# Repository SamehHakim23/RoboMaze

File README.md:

# RoboMaze — Autonomous Maze-Solving Robot

**ECNG 4504 — Embedded Systems for Wireless Communications**  
AUC Spring 2026 | Team 2

---

## Team Members

| Name | Student ID | Email |
|---|---|---|
| Sameh Ahmed | 900211681 | samehahmedhakim@aucegypt.edu |
| Hamza El Meadawy | 900211560 | hamzaelmeadwy@aucegypt.edu |
| Mariam Moataz | 900213249 | mariammoataz@aucegypt.edu |
| Menna AbdelHamed | 900212035 | mennnaa12@aucegypt.edu |

---

## Project Overview

RoboMaze is a fully autonomous maze-solving robot built on the ESP32 microcontroller. It uses a 5-sensor infrared array to follow black lines and navigate a maze autonomously across four sequential runs with no human intervention after the initial start command:

1. **LHR (Run 1)** — Explores the maze using the Left-Hand Rule, recording all junctions and decisions
2. **Back (Run 2)** — Returns to start along a simplified reverse path
3. **Run 2 (Run 3)** — Re-navigates the maze on the shortest discovered path using Manhattan distance heuristic
4. **Back 2 (Run 4)** — Returns to start along the optimized path

A live web application visualizes the maze map in real time and allows full wireless control via WiFi or Bluetooth BLE.

---

## Repository Structure

RoboMaze/
├── Firmware/           # ESP32 C++ source code (PlatformIO + Arduino)
├── Hardware(KiCad)/    # KiCad hardware schematic
├── Webapp/             # React + TypeScript web application
└── Docs/               # Architecture diagrams, contribution docs, team details

---

## Hardware

| Component | Model | Role |
|---|---|---|
| Microcontroller | ESP32 DevKit V1 | Main compute, WiFi 802.11, BLE 4.2 |
| IR Sensors | TCRT5000 × 5 | Line detection array |
| Motor Driver | L298N | Dual H-bridge PWM motor control |
| DC Motors | 25GA370 130RPM × 2 | Differential drive |
| Wheel Encoders | Hall-effect × 2 | Corridor distance measurement |

---

## Firmware

**Platform:** PlatformIO + Arduino Framework  
**Language:** C++  

Key features:
- Left-Hand Rule maze exploration with junction recording
- Triplet path simplification algorithm
- Run 2 Manhattan distance navigation with axis-priority selection
- WebSocket server on port 81 with full JSON telemetry protocol
- BLE GATT server with TX notify and RX write characteristics
- Encoder-based corridor distance measurement with auto-calibration

```ini
lib_deps =
    links2004/WebSockets@^2.4.0
    bblanchon/ArduinoJson@^6.21.0
board_build.partitions = huge_app.csv
```

---

## Web Application

**Stack:** React + TypeScript + Vite (frontend), Express (backend)  
**URL:** robomaze.net

Features:
- Live maze map with proportional corridor rendering
- Real-time sensor display and robot state indicator
- Full robot control panel (start, back, run2, back2, pause, e-stop)
- WiFi mode: direct browser → `ws://172.20.10.9:81`
- BLE mode: Web Bluetooth API (Chrome desktop)

---

## Wireless Communication

| Channel | Details |
|---|---|
| WiFi | Static IP 172.20.10.9 · WebSocket port 81 |
| BLE | Device: RoboMaze · Service UUID: 12345678-1234-1234-1234-123456789abc |
| Telnet | Port 23 · Raw log streaming |

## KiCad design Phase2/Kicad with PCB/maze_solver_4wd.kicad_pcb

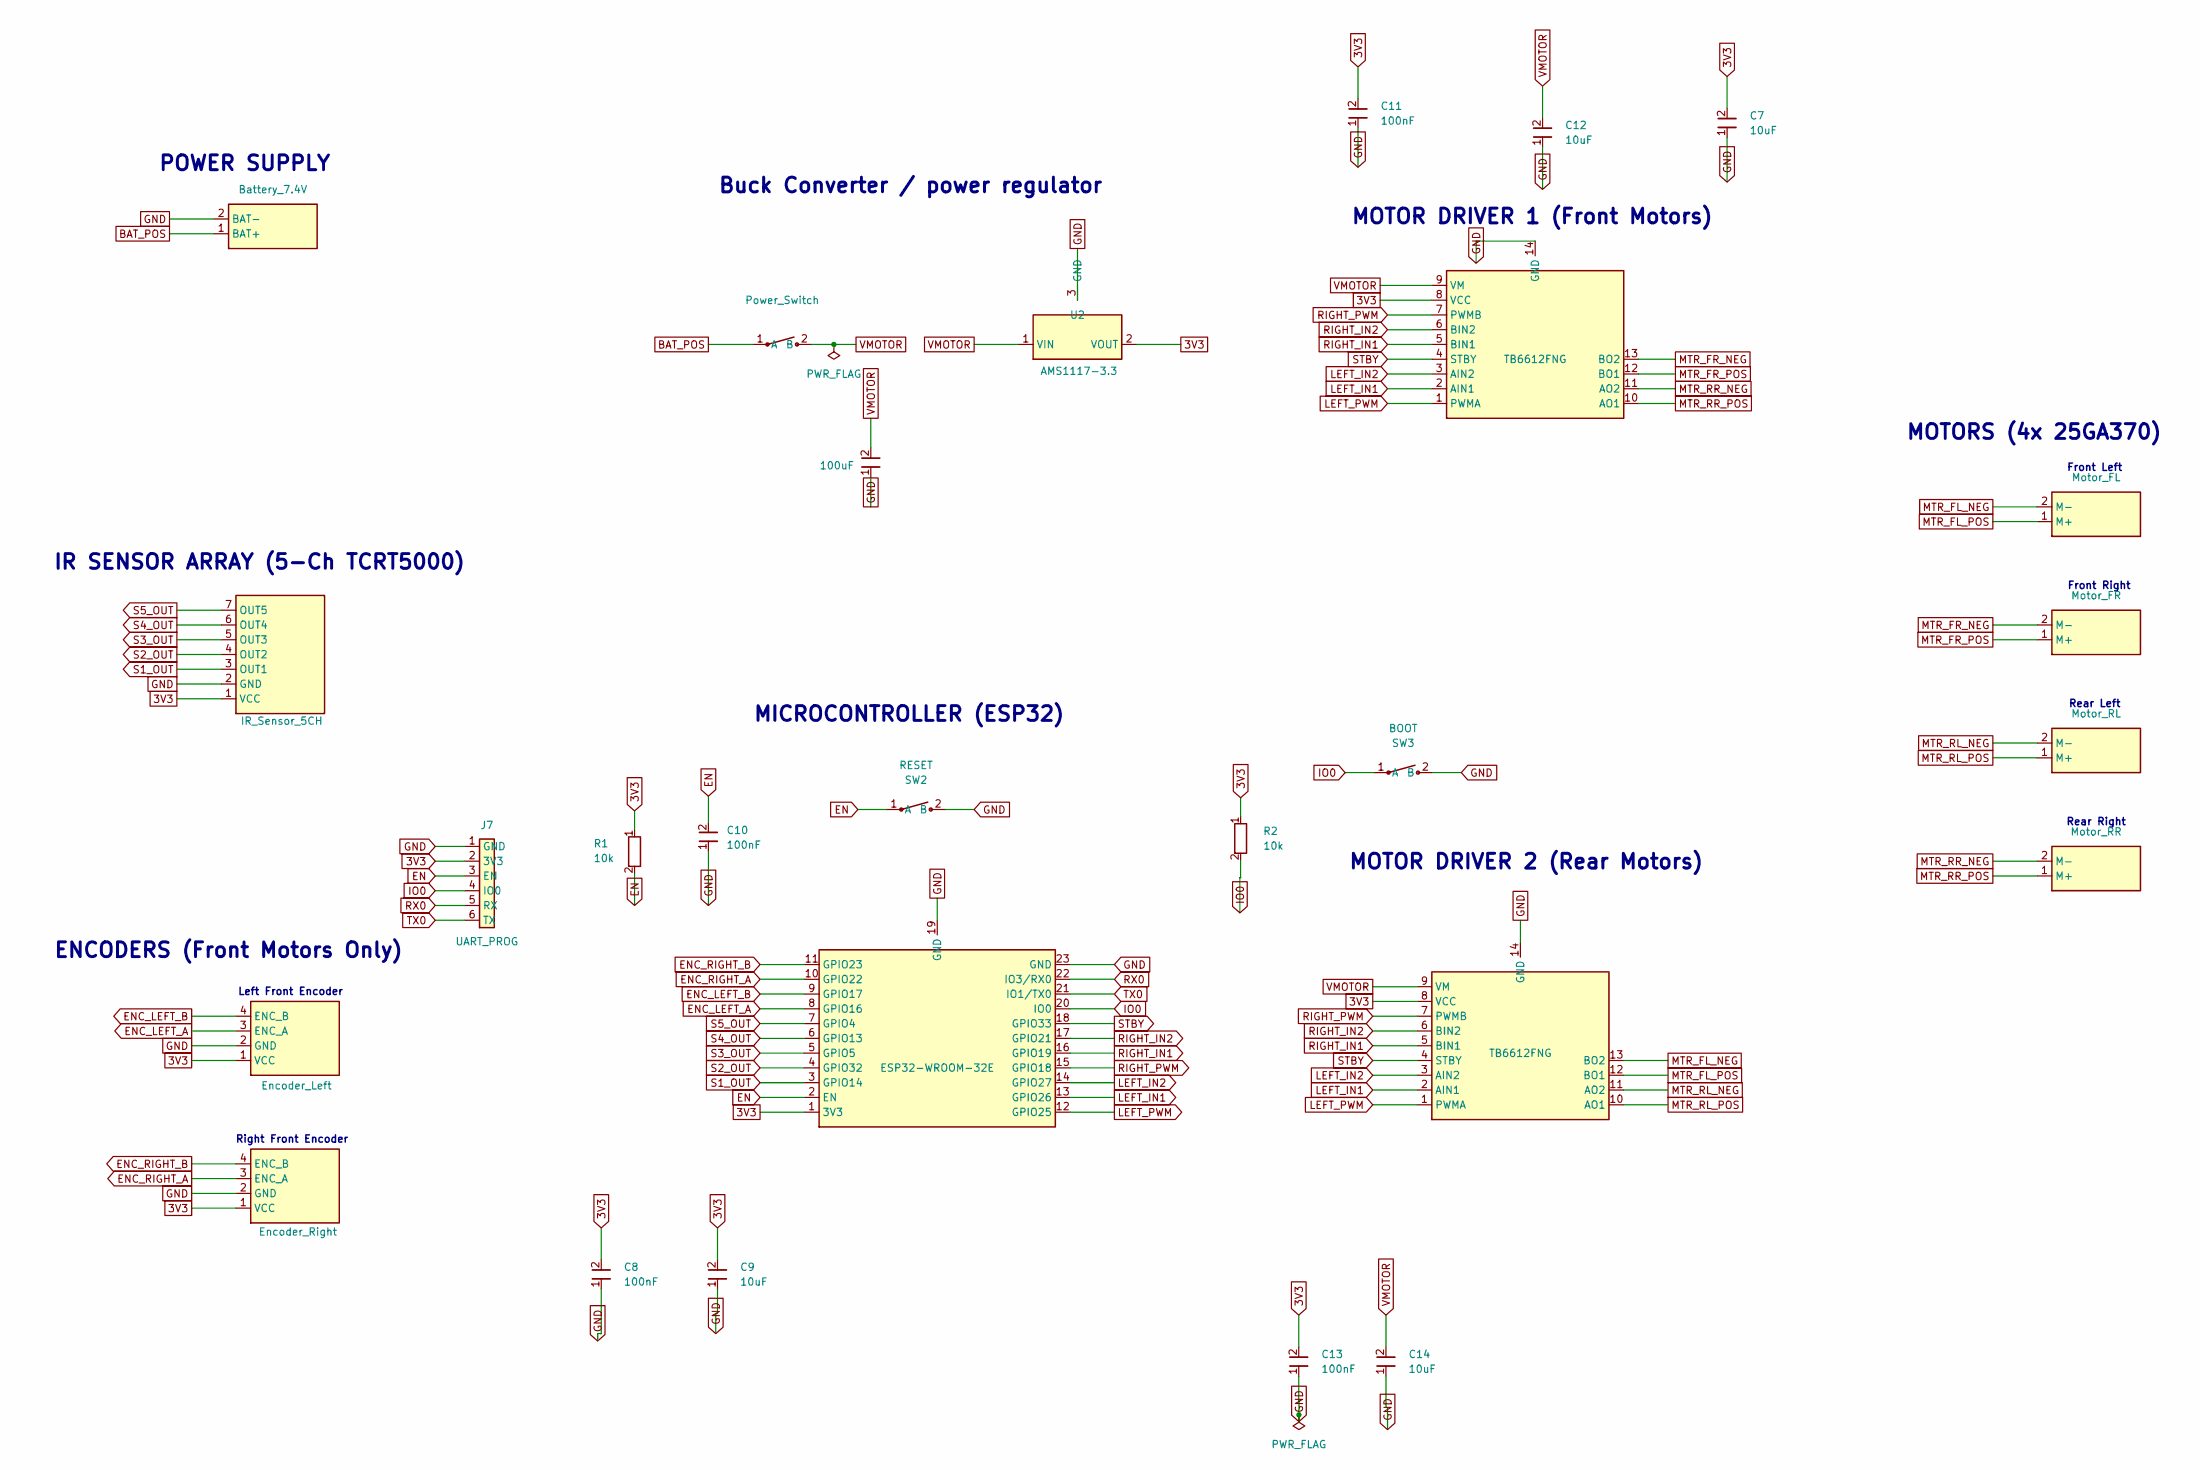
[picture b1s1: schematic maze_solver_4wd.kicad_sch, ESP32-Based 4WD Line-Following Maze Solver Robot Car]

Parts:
C1: 100uF; C_0805_2012Metric
C7, C9, C12, C14: 10uF; C_0805_2012Metric
C8, C10, C11, C13: 100nF; C_0805_2012Metric
J1: Battery_7.4V; JST_PH_S2B-PH-SM4-TB_1x02-1MP_P2.00mm_Horizontal
J2: IR_Sensor_5CH; PinHeader_1x07_P2.54mm_Vertical_SMD_Pin1Left
J3: Encoder_Left; JST_PH_S4B-PH-SM4-TB_1x04-1MP_P2.00mm_Horizontal
J4: Encoder_Right; JST_PH_S4B-PH-SM4-TB_1x04-1MP_P2.00mm_Horizontal
J5: Motor_FL; JST_PH_S2B-PH-SM4-TB_1x02-1MP_P2.00mm_Horizontal
J6: Motor_FR; JST_PH_S2B-PH-SM4-TB_1x02-1MP_P2.00mm_Horizontal
J7: UART_PROG; PinHeader_1x06_P2.54mm_Vertical_SMD_Pin1Left
J8: Motor_RL; JST_PH_S2B-PH-SM4-TB_1x02-1MP_P2.00mm_Horizontal
J9: Motor_RR; JST_PH_S2B-PH-SM4-TB_1x02-1MP_P2.00mm_Horizontal
R1, R2: 10k; R_0805_2012Metric
SW1: Power_Switch; SW_SPDT_PCM12
SW2: RESET; SW_SPST_TL3342
SW3: BOOT; SW_SPST_TL3342
U1: ESP32-WROOM-32E; ESP32-WROOM-32
U2: AMS1117-3.3; SOT-223-3_TabPin2
U3, U4: TB6612FNG; SSOP-24_5.3x8.2mm_P0.65mm

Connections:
3V3: C7.2, C8.2, C9.2, C11.2, C13.2, J2.1 (VCC), J3.1 (VCC), J4.1 (VCC), J7.2 (3V3), R1.1, R2.1, U1.1 (3V3), U2.2 (VOUT), U3.8 (VCC), U4.8 (VCC)
BAT_POS: J1.1 (BAT+), SW1.1 (A)
EN: C10.2, J7.3 (EN), R1.2, SW2.1 (A), U1.2 (EN)
ENC_LEFT_A: J3.3 (ENC_A), U1.8 (GPIO16)
ENC_LEFT_B: J3.4 (ENC_B), U1.9 (GPIO17)
ENC_RIGHT_A: J4.3 (ENC_A), U1.10 (GPIO22)
ENC_RIGHT_B: J4.4 (ENC_B), U1.11 (GPIO23)
GND: C1.1, C7.1, C8.1, C9.1, C10.1, C11.1, C12.1, C13.1, C14.1, J1.2 (BAT-), J2.2 (GND), J3.2 (GND), J4.2 (GND), J7.1 (GND), SW2.2 (B), SW3.2 (B), U1.19 (GND), U1.23 (GND), U2.3 (GND), U3.14 (GND), U4.14 (GND)
IO0: J7.4 (IO0), R2.2, SW3.1 (A), U1.20 (IO0)
LEFT_IN1: U1.13 (GPIO26), U3.2 (AIN1), U4.2 (AIN1)
LEFT_IN2: U1.14 (GPIO27), U3.3 (AIN2), U4.3 (AIN2)
LEFT_PWM: U1.12 (GPIO25), U3.1 (PWMA), U4.1 (PWMA)
MTR_FL_NEG: J5.2 (M-), U3.13 (BO2)
MTR_FL_POS: J5.1 (M+), U3.12 (BO1)
MTR_FR_NEG: J6.2 (M-), U4.13 (BO2)
MTR_FR_POS: J6.1 (M+), U4.12 (BO1)
MTR_RL_NEG: J8.2 (M-), U3.11 (AO2)
MTR_RL_POS: J8.1 (M+), U3.10 (AO1)
MTR_RR_NEG: J9.2 (M-), U4.11 (AO2)
MTR_RR_POS: J9.1 (M+), U4.10 (AO1)
RIGHT_IN1: U1.16 (GPIO19), U3.5 (BIN1), U4.5 (BIN1)
RIGHT_IN2: U1.17 (GPIO21), U3.6 (BIN2), U4.6 (BIN2)
RIGHT_PWM: U1.15 (GPIO18), U3.7 (PWMB), U4.7 (PWMB)
RX0: J7.5 (RX), U1.22 (IO3/RX0)
S1_OUT: J2.3 (OUT1), U1.3 (GPIO14)
S2_OUT: J2.4 (OUT2), U1.4 (GPIO32)
S3_OUT: J2.5 (OUT3), U1.5 (GPIO5)
S4_OUT: J2.6 (OUT4), U1.6 (GPIO13)
S5_OUT: J2.7 (OUT5), U1.7 (GPIO4)
STBY: U1.18 (GPIO33), U3.4 (STBY), U4.4 (STBY)
TX0: J7.6 (TX), U1.21 (IO1/TX0)
VMOTOR: C1.2, C12.2, C14.2, SW1.2 (B), U2.1 (VIN), U3.9 (VM), U4.9 (VM)

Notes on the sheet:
Front Left
Rear Right
Right Front Encoder
Left Front Encoder
Buck Converter / power regulator
MOTORS (4x 25GA370)
POWER SUPPLY
Rear Left
MOTOR DRIVER 1 (Front Motors)
IR SENSOR ARRAY (5-Ch TCRT5000)
MOTOR DRIVER 2 (Rear Motors)
MICROCONTROLLER (ESP32)
Front Right
ENCODERS (Front Motors Only)

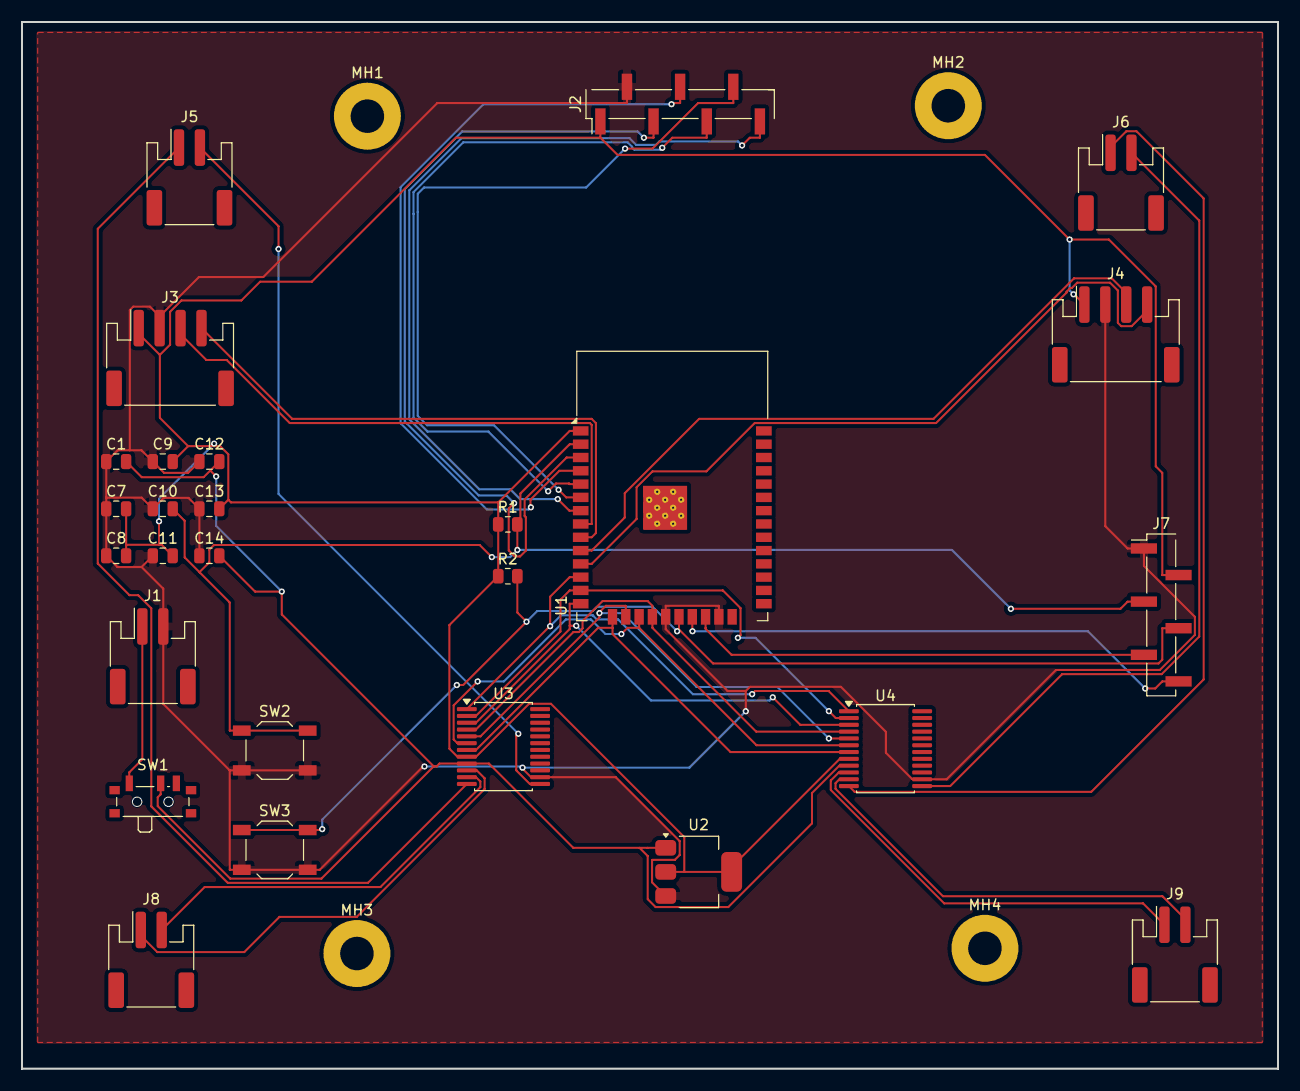
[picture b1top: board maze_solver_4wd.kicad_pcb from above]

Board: 2 copper layers, 120.0 x 100.0 mm, 31 parts (0 on the bottom side), 32 nets.

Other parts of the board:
MH1, MH2, MH3, MH4: MountingHole_3.2mm_M3_Pad

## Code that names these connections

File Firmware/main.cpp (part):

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#include <BLEUtils.h>
#include <BLE2902.h>

#define STBY_PIN  33
#define LEFT_PWM  25
#define LEFT_IN1  26
#define LEFT_IN2  27
#define RIGHT_PWM 18
#define RIGHT_IN1 19
#define RIGHT_IN2 21
#define S1 14
#define S2 32
#define S3 5
#define S4 13
#define S5 4

#define ENC_LEFT_A  16
#define ENC_RIGHT_A 22

#define PWM_FREQ 1000
#define PWM_RES  8
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
void setup() {
  Serial.begin(115200); delay(1000);
  pinMode(STBY_PIN,OUTPUT);
  pinMode(LEFT_IN1,OUTPUT);pinMode(LEFT_IN2,OUTPUT);
  pinMode(RIGHT_IN1,OUTPUT);pinMode(RIGHT_IN2,OUTPUT);
  pinMode(S1,INPUT);pinMode(S2,INPUT);pinMode(S3,INPUT);pinMode(S4,INPUT);pinMode(S5,INPUT);
  ledcSetup(LEFT_CH,PWM_FREQ,PWM_RES); ledcAttachPin(LEFT_PWM,LEFT_CH);
  ledcSetup(RIGHT_CH,PWM_FREQ,PWM_RES); ledcAttachPin(RIGHT_PWM,RIGHT_CH);
  digitalWrite(STBY_PIN,HIGH); stopMotors();
  pinMode(ENC_LEFT_A,INPUT_PULLUP); pinMode(ENC_RIGHT_A,INPUT_PULLUP);
  attachInterrupt(digitalPinToInterrupt(ENC_LEFT_A), isrLeftA, RISING);
  attachInterrupt(digitalPinToInterrupt(ENC_RIGHT_A),isrRightA,RISING);
  Serial.println("[ENC] Interrupts attached");

  BLEDevice::init(BLE_DEVICE_NAME); BLEDevice::setMTU(512);
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
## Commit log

2026-04-16 Initial commit - RoboMaze Phase 0 and Phase 1 deliverables
2026-04-16 Revise README with project overview and team info
    Updated project details, team members, and features.
2026-05-04 Create Phase 2
2026-05-04 Create test
